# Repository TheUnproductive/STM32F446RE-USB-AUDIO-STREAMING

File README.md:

# STM32F446RE-USB-AUDIO-STREAMING
This repository aims to build a USB Audio Interface with the use of a STM32F446RE chip. It serves to distribute knownledge about the USB Audio Streaming feature of the STM32F4 chip family.

## Rules for adding files:
If you want to contribute to this repository push your files to the `experimental` branch.   
Merge requests to the `main` branch are only allowed if the code has been tested by multiple parties.   
Merge requests to the `private-main` branch will be ignored, since it will be used for personal testing and development.

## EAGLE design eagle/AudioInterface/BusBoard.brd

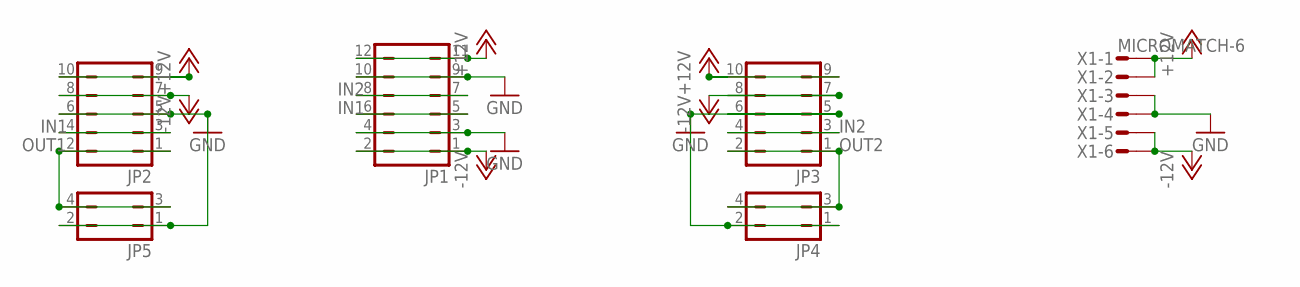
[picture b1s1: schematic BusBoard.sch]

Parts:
JP1: JP6Q
JP2, JP3: JP5Q
JP4, JP5: JP2Q
X1: MICROMATCH-6

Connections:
+12V: JP1.11, JP1.12, JP2.9, JP2.10, JP3.9, JP3.10, X1.1, X1.2
-12V: JP1.1, JP1.2, JP2.7, JP2.8, JP3.7, JP3.8, X1.5, X1.6
GND: JP1.3, JP1.4, JP1.9, JP1.10, JP2.5, JP2.6, JP3.5, JP3.6, JP4.1, JP4.2, JP5.1, JP5.2, X1.3, X1.4
IN1: JP1.5, JP1.6, JP2.3, JP2.4
IN2: JP1.7, JP1.8, JP3.3, JP3.4
OUT1: JP2.1, JP2.2, JP5.3, JP5.4
OUT2: JP3.1, JP3.2, JP4.3, JP4.4

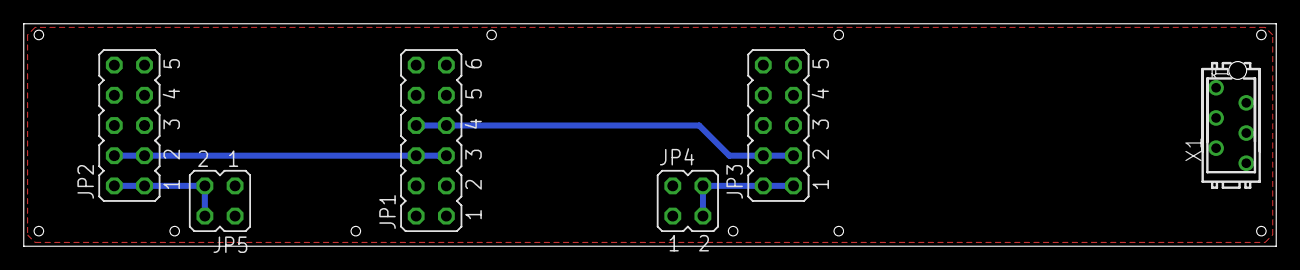
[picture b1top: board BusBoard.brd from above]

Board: 4 copper layers, 105.4 x 18.7 mm, 6 parts (0 on the bottom side), 7 nets.

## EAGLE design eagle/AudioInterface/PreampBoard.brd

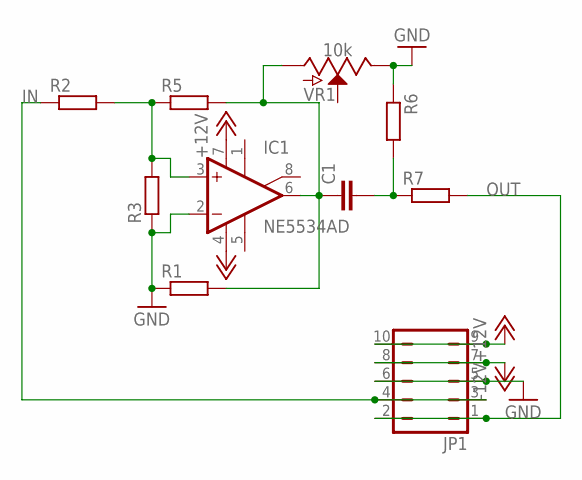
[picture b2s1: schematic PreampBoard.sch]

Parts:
C1: C-EUC0805; C0805
IC1: NE5534AD; SO08
JP1: JP5Q
R1, R2, R3, R5, R6, R7: R-EU_R0805; R0805
VR1: 10k; POT-PTH-ALPS

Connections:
+12V: IC1.7 (V+), JP1.9, JP1.10
-12V: IC1.4 (V-), JP1.7, JP1.8
GND: IC1.2 (-IN), JP1.5, JP1.6, R1.1, R3.1, R6.1, VR1.P$1 (E)
IN: JP1.3, JP1.4, R2.1
unnamed: C1.1, IC1.6 (OUT), R1.2, R5.2, VR1.P$3 (A)
unnamed: IC1.3 (+IN), R2.2, R3.2, R5.1
unnamed: C1.2, R6.2, R7.1
OUT: JP1.1, JP1.2, R7.2

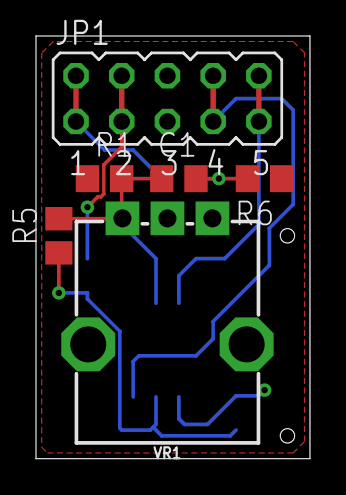
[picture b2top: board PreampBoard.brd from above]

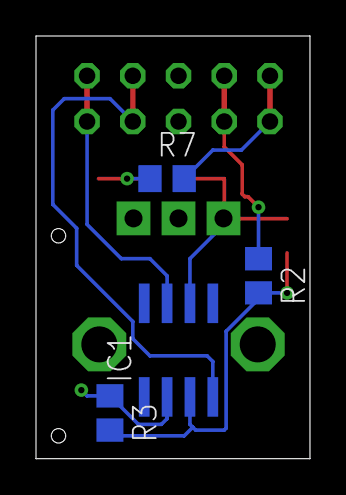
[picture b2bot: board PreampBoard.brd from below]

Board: 2 copper layers, 15.2 x 23.5 mm, 10 parts (4 on the bottom side), 8 nets.

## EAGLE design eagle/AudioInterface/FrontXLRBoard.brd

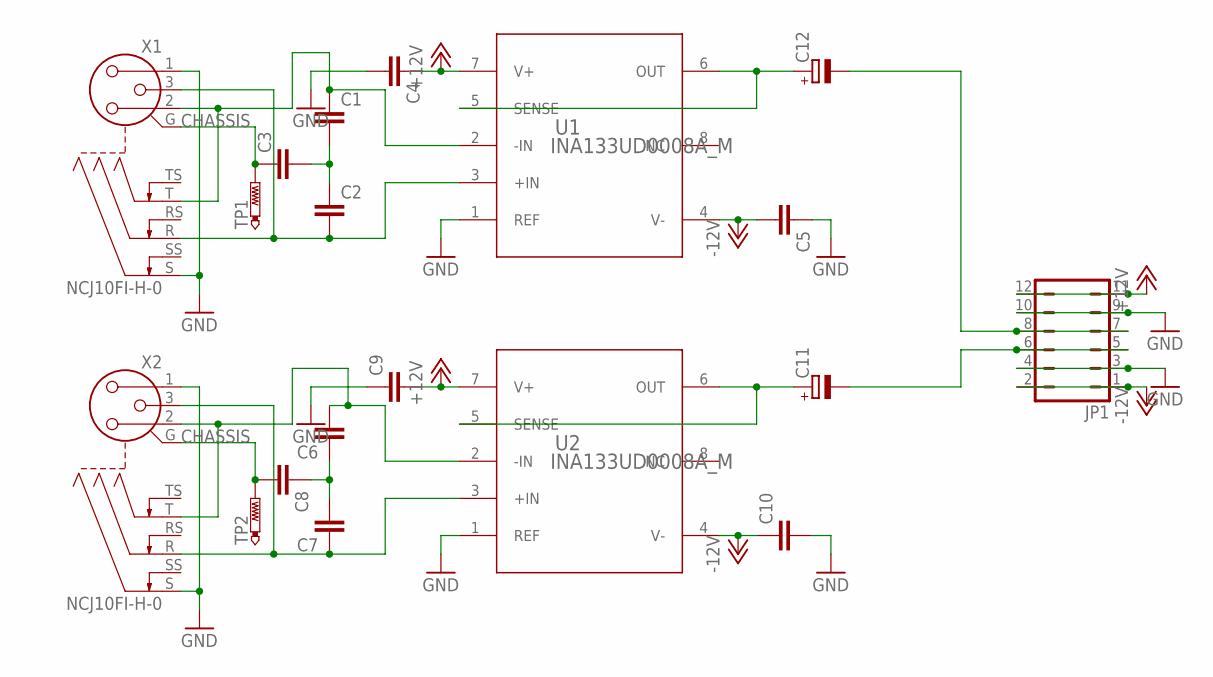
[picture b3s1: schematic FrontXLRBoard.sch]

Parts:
C1, C2, C3, C4, C5, C6, C7, C8, C9, C10: C-EUC0805; C0805
C11, C12: CPOL-EU153CLV-0807; 153CLV-0807
JP1: JP6Q
TP1, TP2: PTR1PAD1-17; P1-17
U1, U2: INA133UD0008A_M; D0008A_M
X1, X2: NCJ10FI-H-0

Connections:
+12V: C4.1, C9.2, JP1.11, JP1.12, U1.7 (V+), U2.7 (V+)
-12V: C5.2, C10.1, JP1.1, JP1.2, U1.4 (V-), U2.4 (V-)
CHASSIS: C3.1, C8.2, TP1.TP, TP2.TP, X1.G, X2.G
GND: C4.2, C5.1, C9.1, C10.2, JP1.3, JP1.4, JP1.9, JP1.10, U1.1 (REF), U2.1 (REF), X1.1, X1.S, X2.1, X2.S
unnamed: C2.2, U1.3 (+IN), X1.3, X1.R
unnamed: C1.2, C2.1, C3.2
unnamed: C1.1, U1.2 (-IN), X1.2, X1.T
unnamed: C12.-, JP1.7, JP1.8
unnamed: C6.1, C7.2, C8.1
unnamed: C6.2, U2.2 (-IN), X2.2, X2.T
unnamed: C7.1, U2.3 (+IN), X2.3, X2.R
unnamed: C12.+, U1.5 (SENSE), U1.6 (OUT)
unnamed: C11.+, U2.5 (SENSE), U2.6 (OUT)
unnamed: C11.-, JP1.5, JP1.6

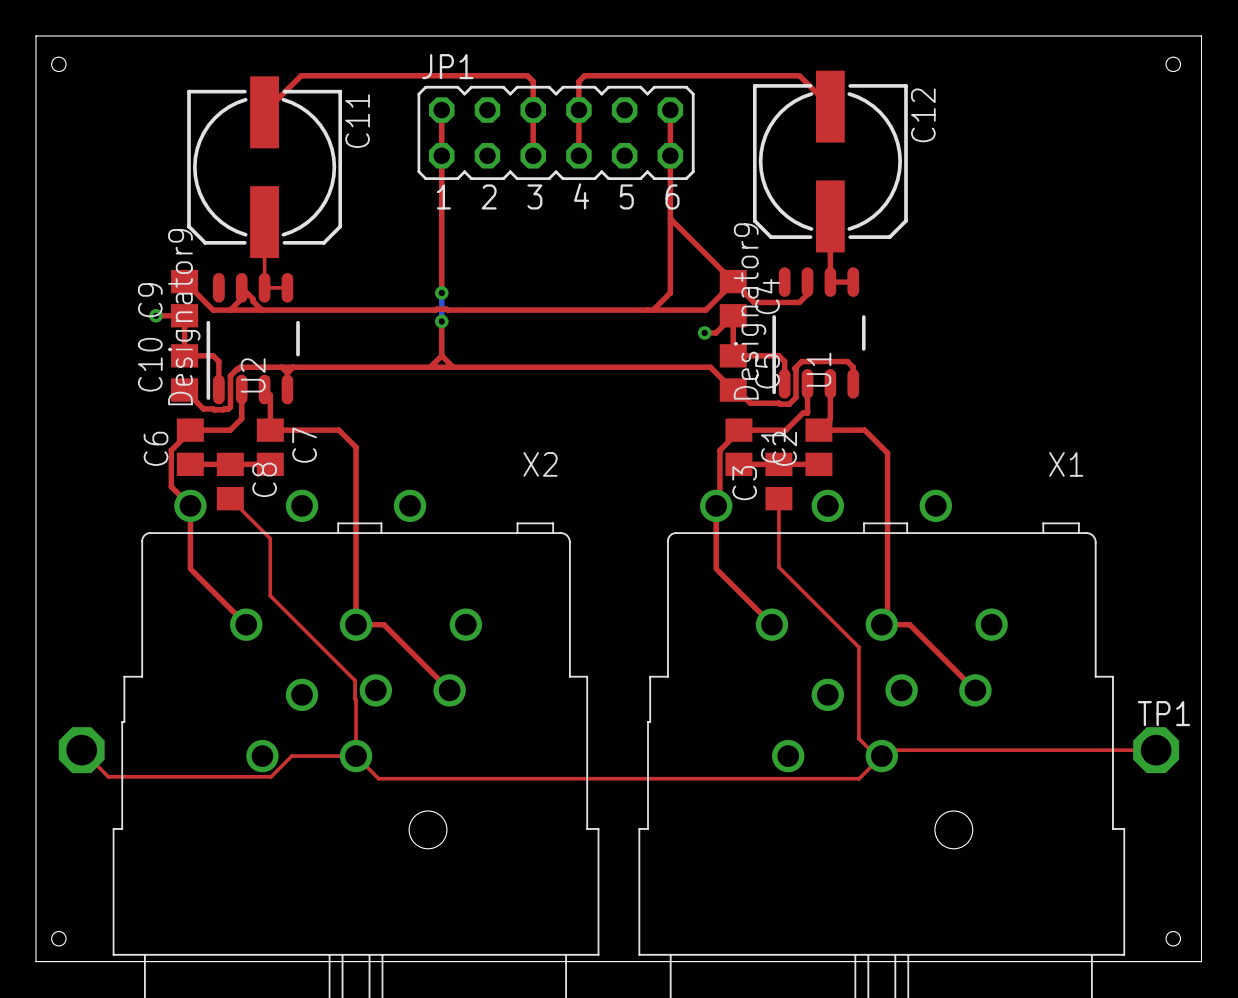
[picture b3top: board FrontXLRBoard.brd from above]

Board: 2 copper layers, 64.8 x 51.4 mm, 19 parts (1 on the bottom side), 14 nets.

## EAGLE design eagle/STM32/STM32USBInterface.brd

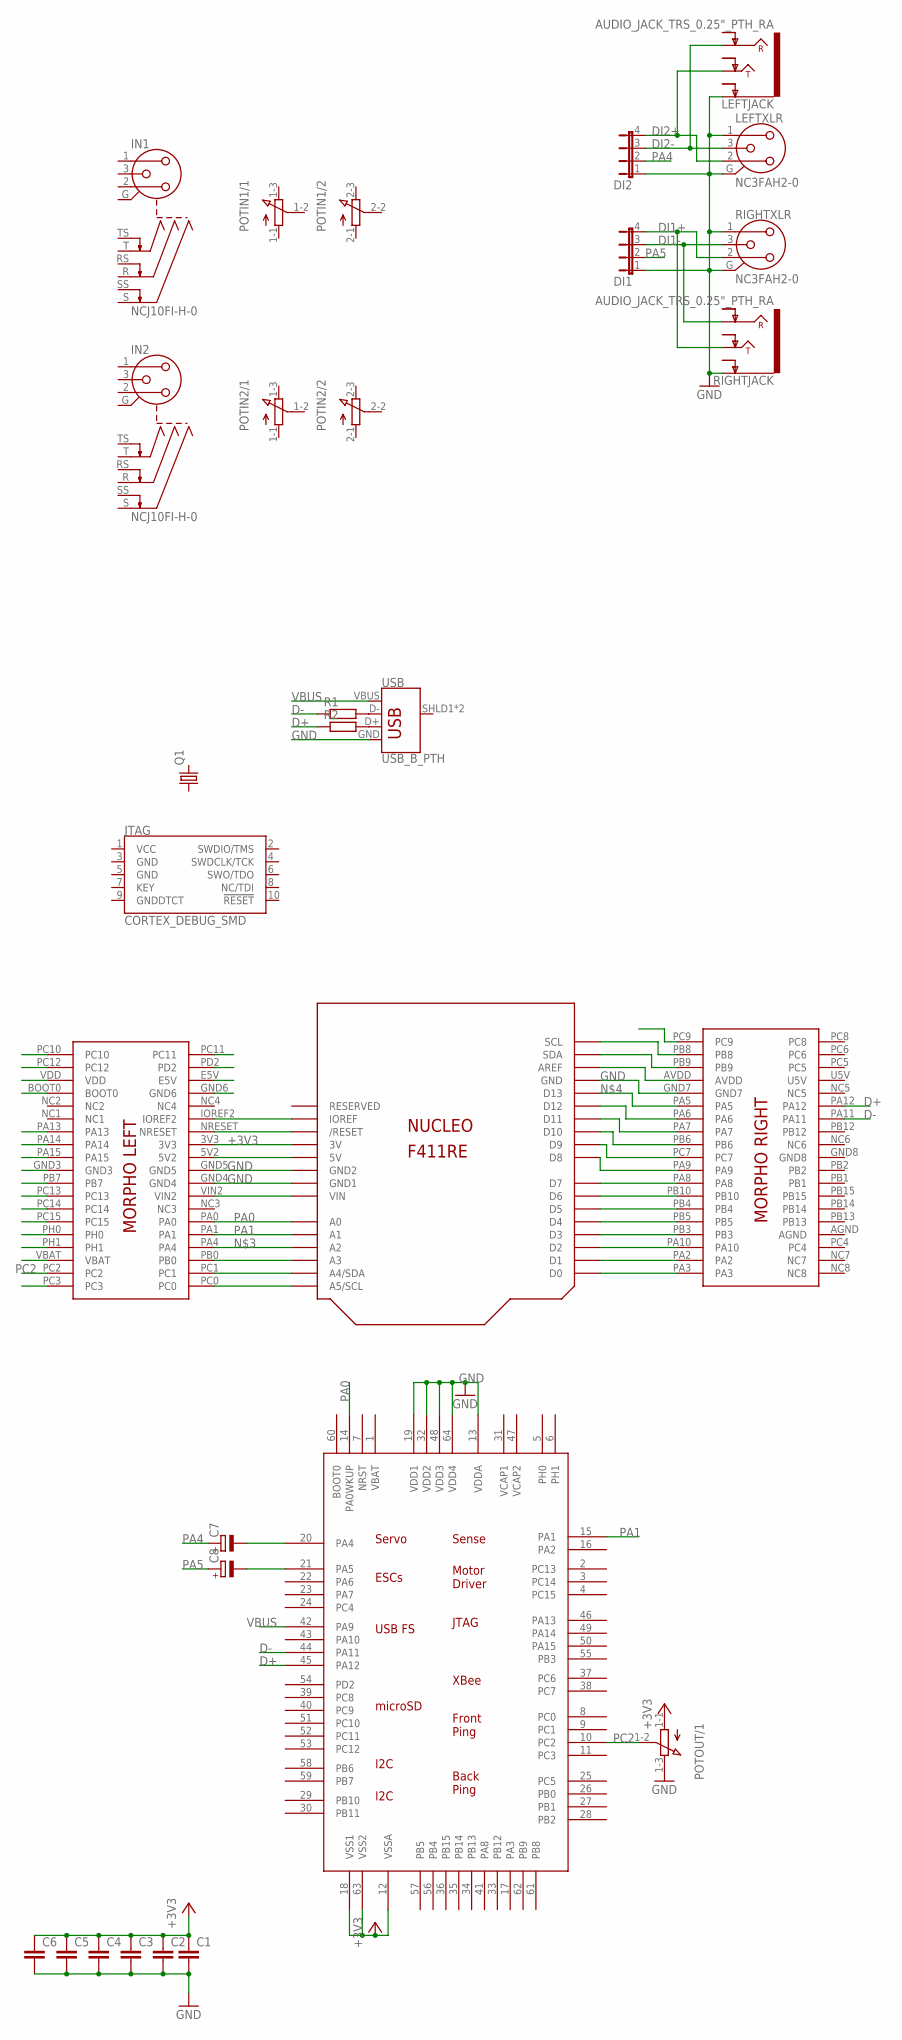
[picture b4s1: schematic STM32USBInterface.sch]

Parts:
C1, C2, C3, C4, C5, C6: C-EUC0805; C0805
C7, C8: CPOL-EUE5-8.5; E5-8,5
DI1, DI2: JP4E; JP4
IN1, IN2: NCJ10FI-H-0
JTAG: CORTEX_DEBUG_SMD; SAMTECH_FTSH-105-01
LEFTJACK: AUDIO_JACK_TRS_0.25"_PTH_RA; AUDIO_JACK_0.25"_TRS_PTH_RA
LEFTXLR: NC3FAH2-0
POTIN1, POTIN2: 3RP/1610G
POTOUT: 3RP/1610G
Q1: CRYSTALCTS406; CTS406
R1, R2: R-EU_R0805; R0805
RIGHTJACK: AUDIO_JACK_TRS_0.25"_PTH_RA; AUDIO_JACK_0.25"_TRS_PTH_RA
RIGHTXLR: NC3FAH2-0
U$1: NUCLEO_F411RE; NUCLEO_BRD64
U$2: STM32F4R_64PIN_FOXCAR; LQFP64
USB: USB_B_PTH; USB-B-PTH

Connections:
+3V3: C1.1, C2.1, C3.1, C4.1, C5.1, C6.1, POTOUT.1-1 (A), U$1.3V, U$1.3V3, U$2.12 (VSSA), U$2.18 (VSS1), U$2.63 (VSS2)
AGND: U$1.AGND
D+: R2.1, U$1.PA12, U$2.45 (PA12)
D-: R1.1, U$1.PA11, U$2.44 (PA11)
DI1+: DI1.4, RIGHTJACK.TIP, RIGHTXLR.2
DI1-: DI1.3, RIGHTJACK.RING, RIGHTXLR.3
DI2+: DI2.4, LEFTJACK.TIP, LEFTXLR.2
DI2-: DI2.3, LEFTJACK.RING, LEFTXLR.3
GND: C1.2, C2.2, C3.2, C4.2, C5.2, C6.2, DI1.1, DI2.1, LEFTJACK.SLEEVE (EARTH), LEFTXLR.1, LEFTXLR.G, POTOUT.1-3 (E), RIGHTJACK.SLEEVE (EARTH), RIGHTXLR.1, RIGHTXLR.G, U$1.GND, U$1.GND1, U$1.GND2, U$1.GND4, U$1.GND5, U$1.GND7, U$2.13 (VDDA), U$2.19 (VDD1), U$2.32 (VDD2), U$2.48 (VDD3), U$2.64 (VDD4), USB.GND
GND8: U$1.GND8
unnamed: R1.2, USB.D-
unnamed: R2.2, USB.D+
unnamed: C7.-, U$1.A2, U$1.PA4, U$2.20 (PA4)
unnamed: C8.-, U$1.D13, U$1.PA5, U$2.21 (PA5)
unnamed: U$1.A3, U$1.PB0
unnamed: U$1.A4 (A4/SDA), U$1.PC1
unnamed: U$1.A5 (A5/SCL), U$1.PC0
unnamed: U$1.VIN, U$1.VIN2
unnamed: U$1.5V, U$1.5V2
unnamed: U$1.NRESET, U$1.RESET (/RESET)
unnamed: U$1.IOREF, U$1.IOREF2
unnamed: U$1.D0, U$1.PA3
unnamed: U$1.D1, U$1.PA2
unnamed: U$1.D2, U$1.PA10
unnamed: U$1.D3, U$1.PB3
unnamed: U$1.D4, U$1.PB5
unnamed: U$1.D5, U$1.PB4
unnamed: U$1.D6, U$1.PB10
unnamed: U$1.D7, U$1.PA8
unnamed: U$1.D8, U$1.PA9
unnamed: U$1.D9, U$1.PC7
unnamed: U$1.D10, U$1.PB6
unnamed: U$1.D11, U$1.PA7
unnamed: U$1.D12, U$1.PA6
unnamed: U$1.AREF, U$1.AVDD
unnamed: U$1.PB9, U$1.SDA
unnamed: U$1.PB8, U$1.SCL
PA0: U$1.A0, U$1.PA0, U$2.14 (PA0WKUP)
PA1: U$1.A1, U$1.PA1, U$2.15 (PA1)
PA4: C7.+, DI2.2
PA5: C8.+, DI1.2
PC2: POTOUT.1-2 (S), U$1.PC2, U$2.10 (PC2)
U5V: U$1.U5V
VBUS: U$2.42 (PA9), USB.VBUS

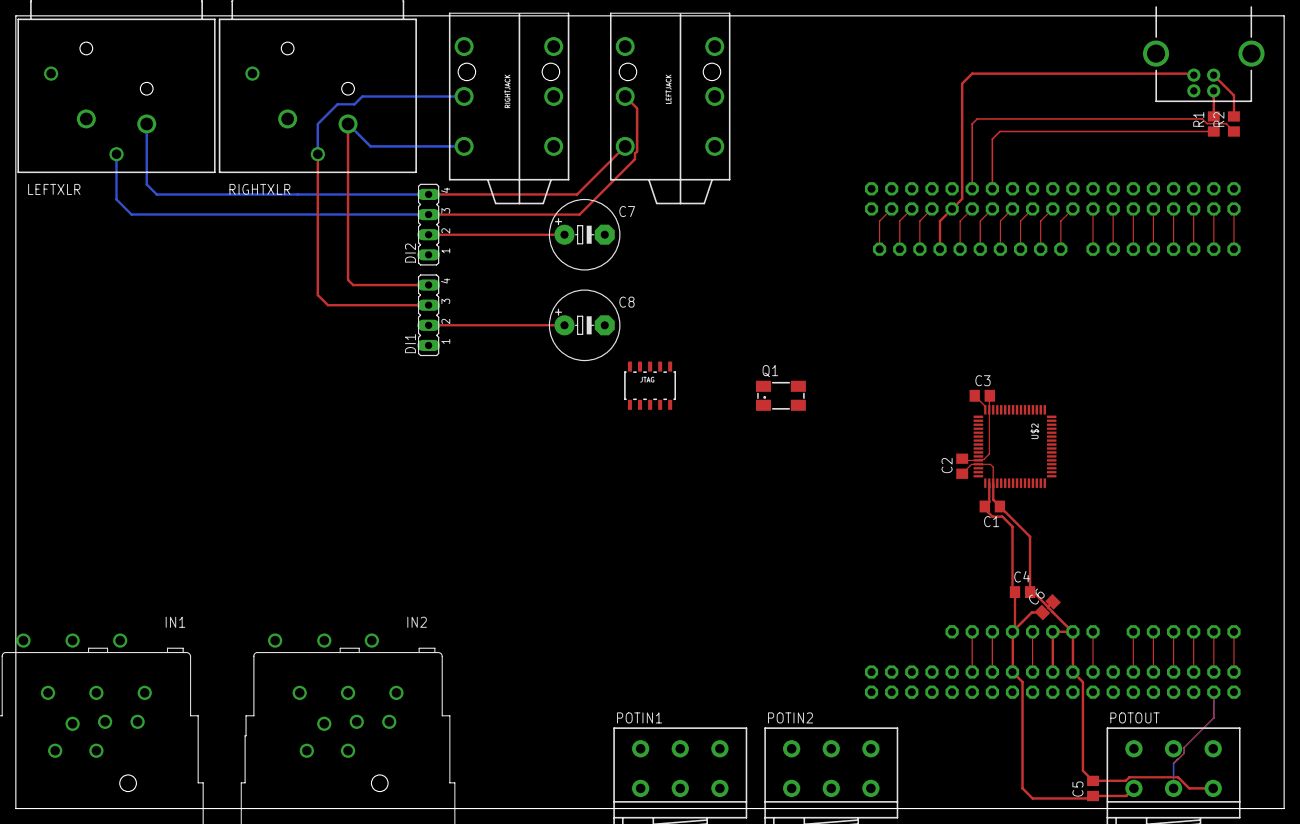
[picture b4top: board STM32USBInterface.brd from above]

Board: 2 copper layers, 160.0 x 100.0 mm, 26 parts (0 on the bottom side), 41 nets.

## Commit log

2021-11-02 Update README.md
    Updated linebreaks
2021-11-02 Pull updated Readme.md into private-main (#1)
    * Update README.md
    * Update README.md
    Updated linebreaks
2021-11-02 Pull updated Readme.md into private-main (#1) (#2)
    * Update README.md
    * Update README.md
    Updated linebreaks
2021-11-02 Pull updated Readme.md into private-main (#1) (#3)
    * Update README.md
    * Update README.md
    Updated linebreaks
2021-11-03 Uploaded Eagle Files
2021-11-03 Pull updated (#4)
    * Update README.md
    * Update README.md
    Updated linebreaks
    * Pull updated Readme.md into private-main (#1) (#2)
    * Update README.md
    * Update README.md
2021-11-03 Commit new folders
2021-11-03 Update Experimental Structure (#5)
    * Update README.md
    * Update README.md
    Updated linebreaks
    * Pull updated Readme.md into private-main (#1) (#2)
    * Update README.md
    * Update README.md
2021-11-03 Experimental (#6)
    * Pull updated Readme.md into private-main (#1) (#3)
    * Update README.md
    * Update README.md
    Updated linebreaks
    * Pull updated (#4)
    * Update README.md
2021-11-10 Added Updated Schematic and Board Design
2021-11-10 Added updated Schematics and Board Design
2021-11-10 Added Libraries to private-main Branch
2021-11-10 Merge updated Schematics (#7)
    Added Updated Schematic and Board Design

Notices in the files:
parts and their libraries:
COPYRIGHT: Copyright (C) 2021 Ultra Librarian. All rights reserved.
SparkFun-Resistors: Licensing: Creative Commons ShareAlike 4.0 International - https://creativecommons.org/licenses/by-sa/4.0
